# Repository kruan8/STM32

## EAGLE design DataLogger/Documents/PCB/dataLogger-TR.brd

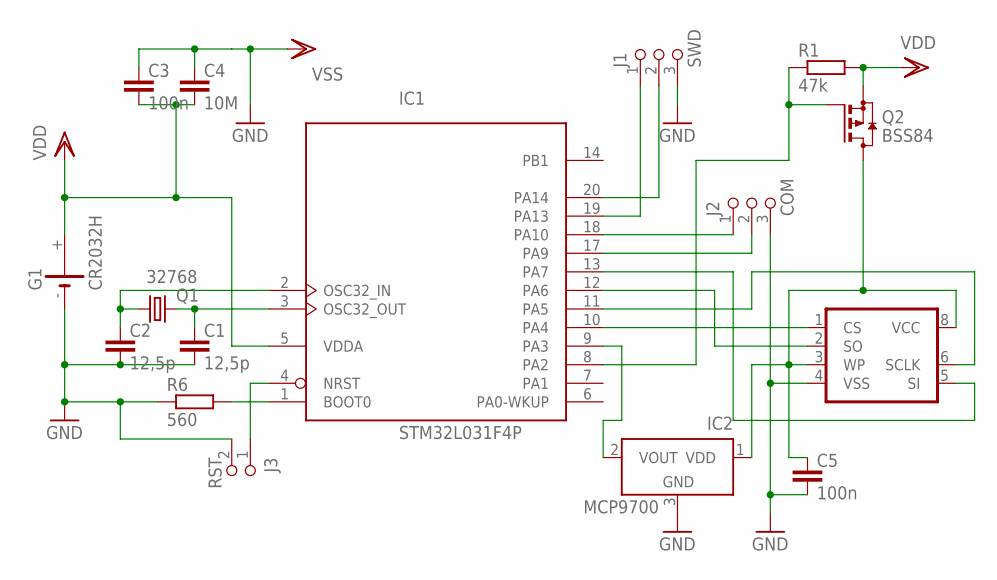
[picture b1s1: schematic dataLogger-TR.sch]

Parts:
C1, C2: 12,5p; 0805
C3, C5: 100n; 0805
C4: 10M; 0805
G1: CR2032H
IC1: STM32L031F4P; TSSOP20-I
IC2: MCP9700; SOT23
J1: SWD; HEAD1X3I
J2: COM; HEAD1X3I
J3: RST; HEAD1X2I
Q1: 32768; TC38H-SMD
Q2: BSS84; SOT23
R1: 47k; R0805
R6: 560; R0805
U$1: GD25; SO08

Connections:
GND: C1.2, C2.2, C3.1, C4.1, C5.2, G1.-, IC1.15 (VSS), IC2.3 (GND), J1.3, J2.3, J3.2, R6.1, U$1.4 (VSS)
unnamed: IC1.1 (BOOT0), R6.2
unnamed: IC1.4 (NRST), J3.1
unnamed: IC1.10 (PA4), U$1.1 (CS)
unnamed: IC1.20 (PA14), J1.2
unnamed: IC1.19 (PA13), J1.1
unnamed: IC1.18 (PA10), J2.1
unnamed: IC1.17 (PA9), J2.2
unnamed: IC1.8 (PA2), Q2.1 (G), R1.1
unnamed: IC1.11 (PA5), U$1.6 (SCLK)
unnamed: IC1.13 (PA7), U$1.5 (SI)
unnamed: IC1.12 (PA6), U$1.2 (SO)
unnamed: IC1.9 (PA3), IC2.2 (VOUT)
unnamed: C2.1, IC1.2 (OSC32_IN), Q1.P$1 (1)
unnamed: C1.1, IC1.3 (OSC32_OUT), Q1.P$2 (2)
unnamed: C5.1, IC2.1 (VDD), Q2.3 (D), U$1.3 (WP), U$1.8 (VCC)
VDD: C3.2, C4.2, G1.+, IC1.5 (VDDA), IC1.16 (VDD), Q2.2 (S), R1.2

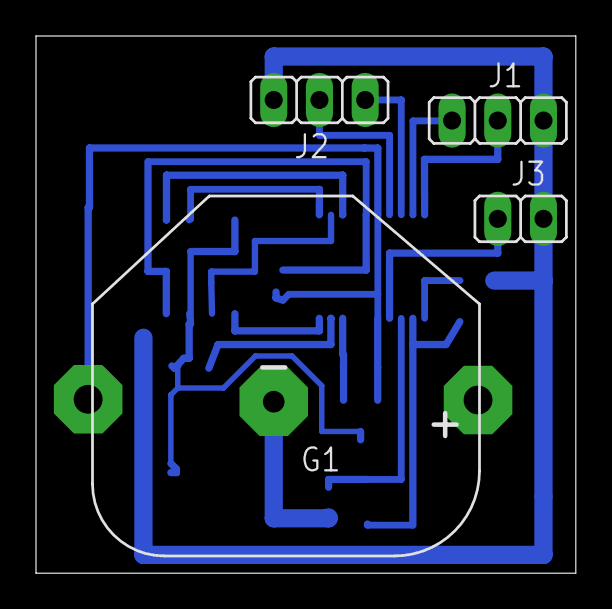
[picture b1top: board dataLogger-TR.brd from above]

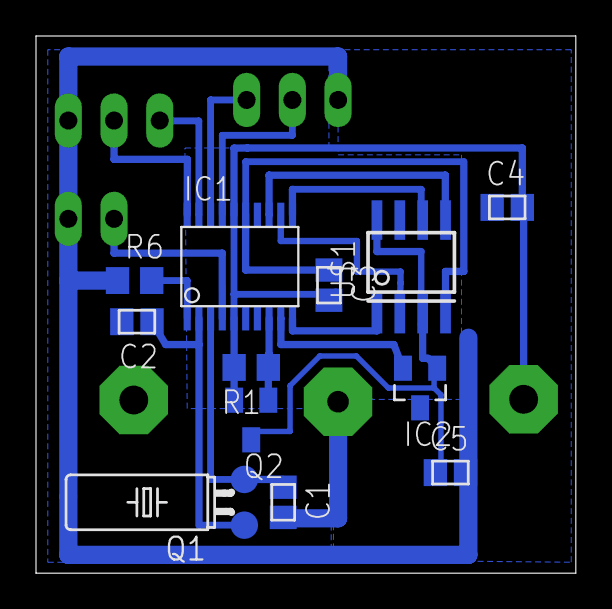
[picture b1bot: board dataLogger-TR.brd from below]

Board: 2 copper layers, 30.0 x 29.8 mm, 16 parts (12 on the bottom side), 17 nets.

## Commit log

2016-08-29 eeprom function
2016-08-30 zaloha
2016-10-11 změna registru pro 915 MHz
2016-10-25 upravy - nechce vysilat
2016-11-08 zmena datumu a casu po USARTu
2016-11-09 STOP mode
2016-11-09 new App file
2016-11-10 RTC - 28bit timestamp
2016-11-10 project created
2016-11-11 Ukladani a vycitani dat
2016-11-14 opravy nedodelku
2016-11-15 STOP mode = 1uA, oprava chyby datumu, doplneni helpu
2016-11-15 problem s prestupnym rokem
2016-11-21 oprava vypoctu datumu, prepocet ADC hodnoty podle VDDA
2016-11-22 zjednoduseni RTC modulu
2016-11-23 change of the record length, add internal thermo sensor, flash driver changed for other flash types
2016-11-24 calibration to EEPROM
2016-11-27 drobne upravy
2016-11-28 Packet filtering removed
2016-11-29 Radio init edited
2016-11-29 drobne zmeny
2016-11-29 USART DeInit added
2016-11-29 Programming mode edited
2016-11-29 Revert "drobne zmeny"
    This reverts commit 87007c890491ac68338b44c86a66b7d42fa9be4e.
2016-11-30 unix timestamp added
2016-12-01 detekce flash opravena
2016-12-05 oprava vypisu záporných teplot, ukládání intervalu do EEPROM
2016-12-05 oprava
2016-12-05 VDDA log changed to precision of 2
2016-12-07 email added
2016-12-08 release config edited
2016-12-08 SPIRIT1 library manual added
2016-12-21 oversampling
2016-12-22 calibration offset added
2016-12-22 some little changes
2017-01-02 oprava chyby vypisu 'List' pri inicializaci vynulovan ukazatel pozice USART bufferu
2017-01-02 add documents
2017-01-03 add touch panel (XPT) documents
2017-01-04 testovaci commit
2017-01-05 oprava velikosti FLASH pameti pri vymazu
2017-01-10 interval corrected -1s
2017-01-18 pridany PCB soubory
2017-01-20 added UGUI pdf + little changes
2017-01-23 SPI and TOUCH controler driver added
